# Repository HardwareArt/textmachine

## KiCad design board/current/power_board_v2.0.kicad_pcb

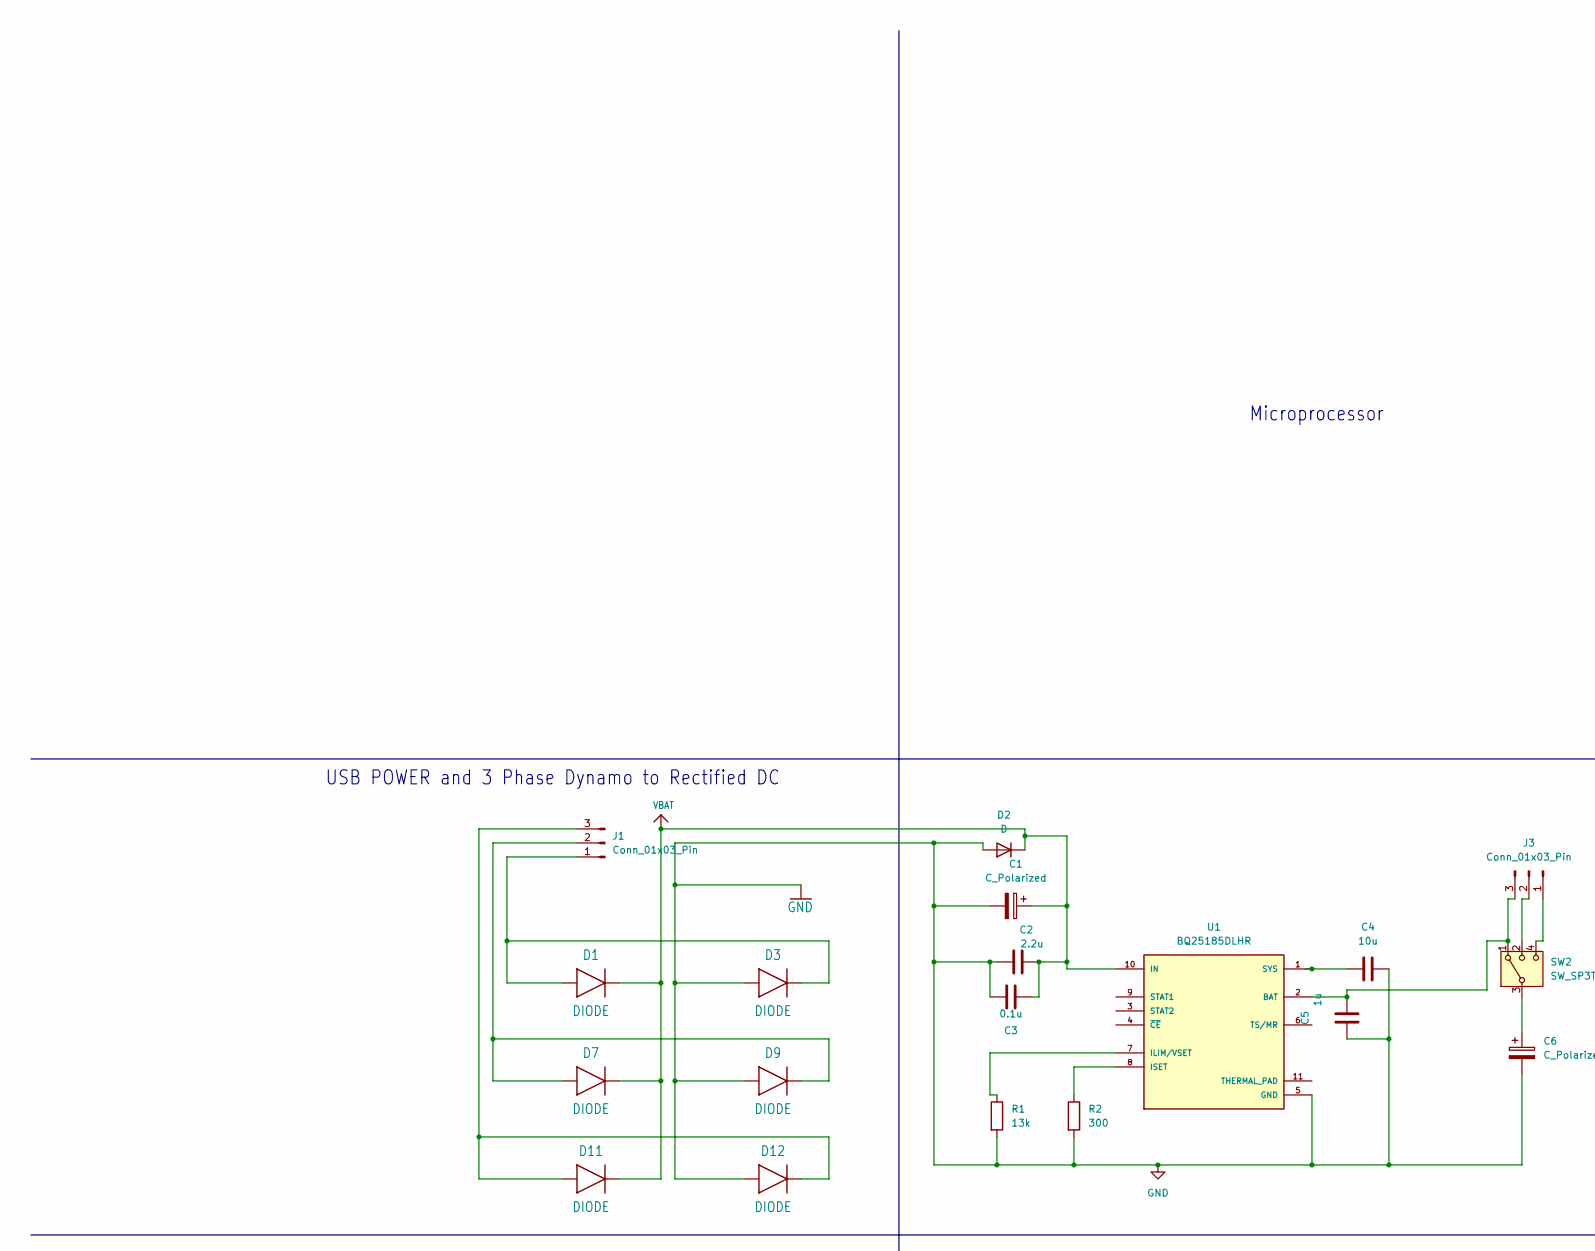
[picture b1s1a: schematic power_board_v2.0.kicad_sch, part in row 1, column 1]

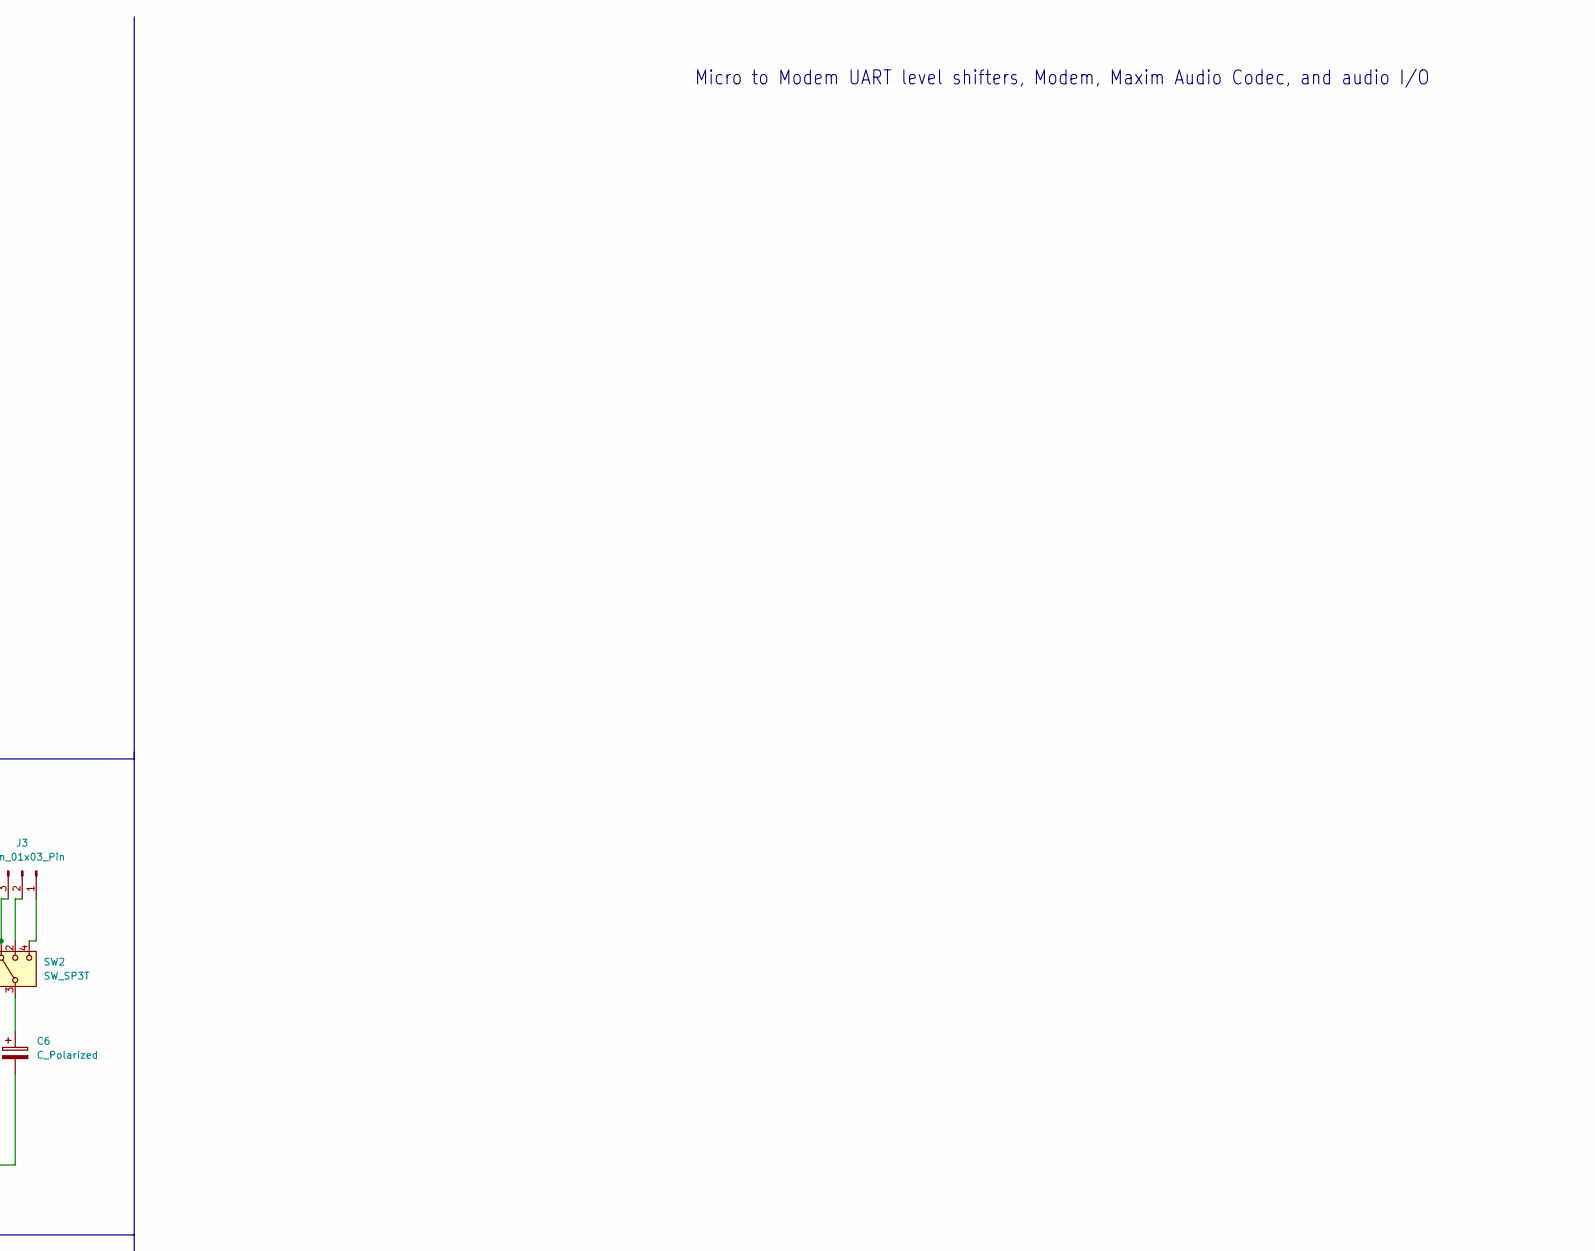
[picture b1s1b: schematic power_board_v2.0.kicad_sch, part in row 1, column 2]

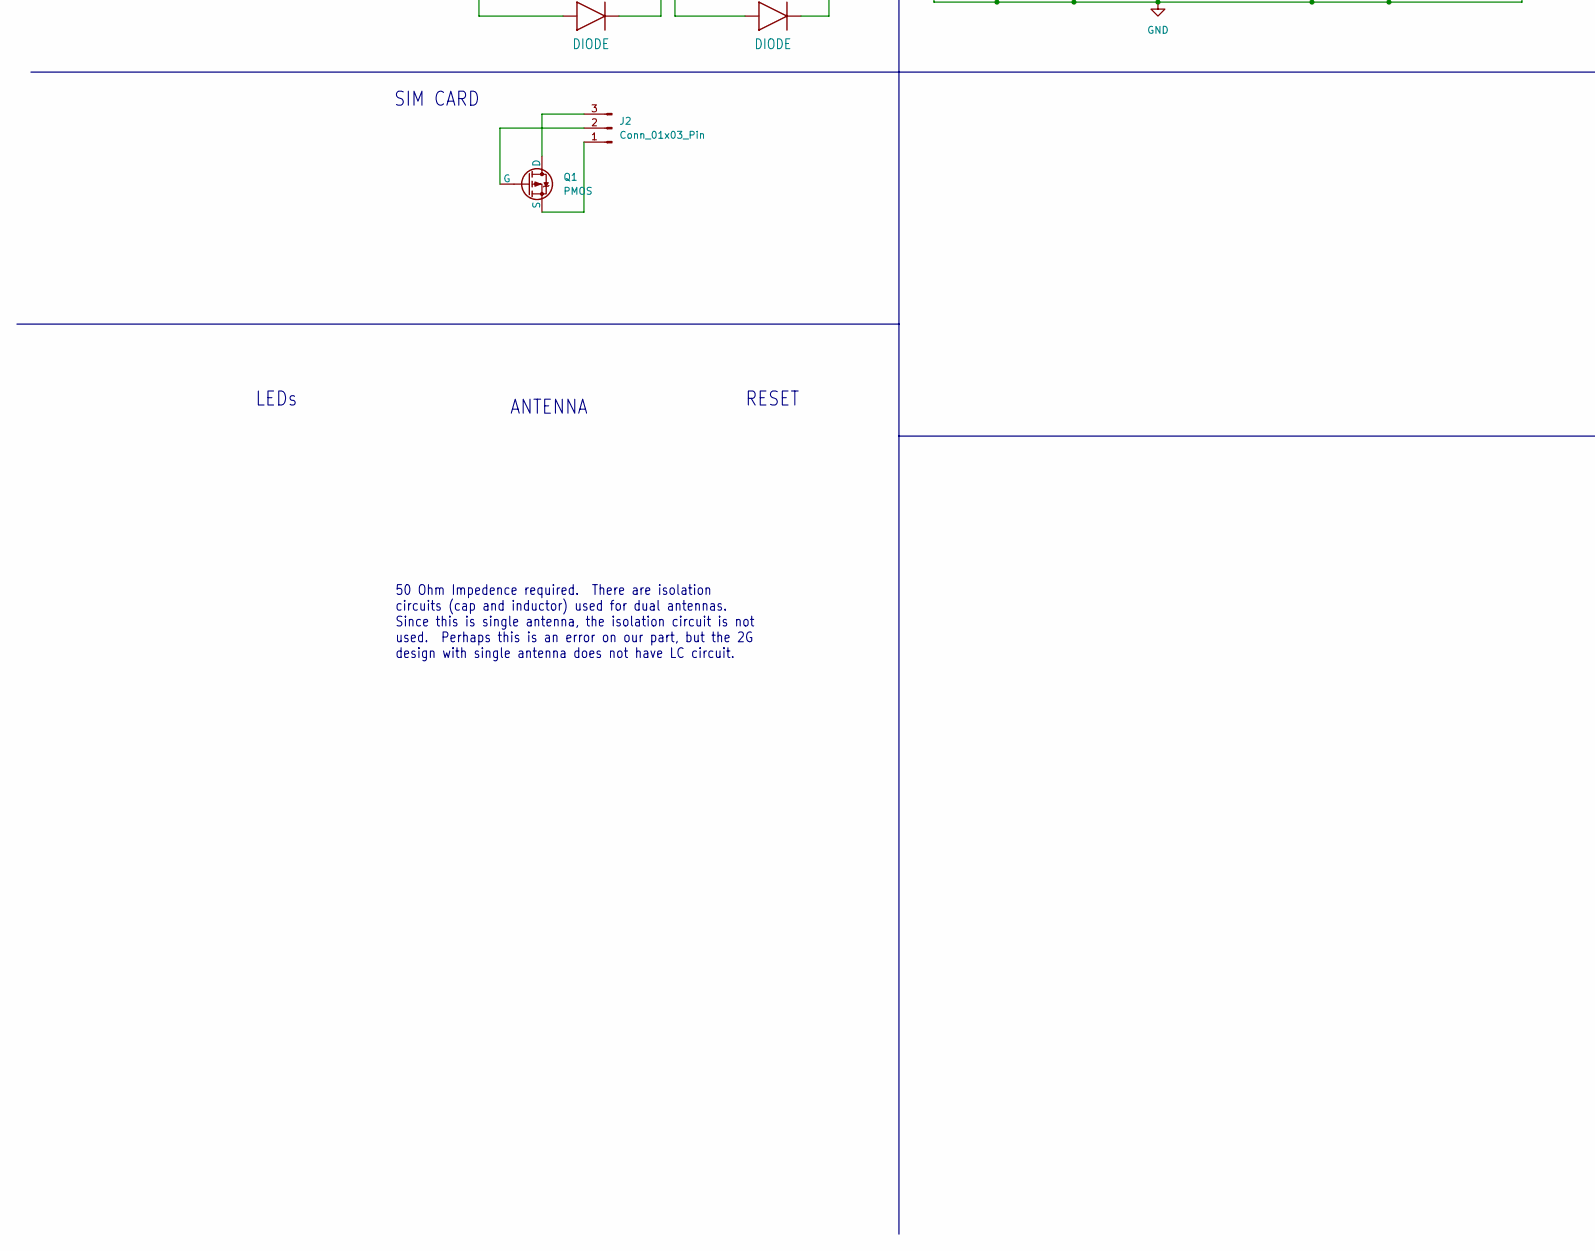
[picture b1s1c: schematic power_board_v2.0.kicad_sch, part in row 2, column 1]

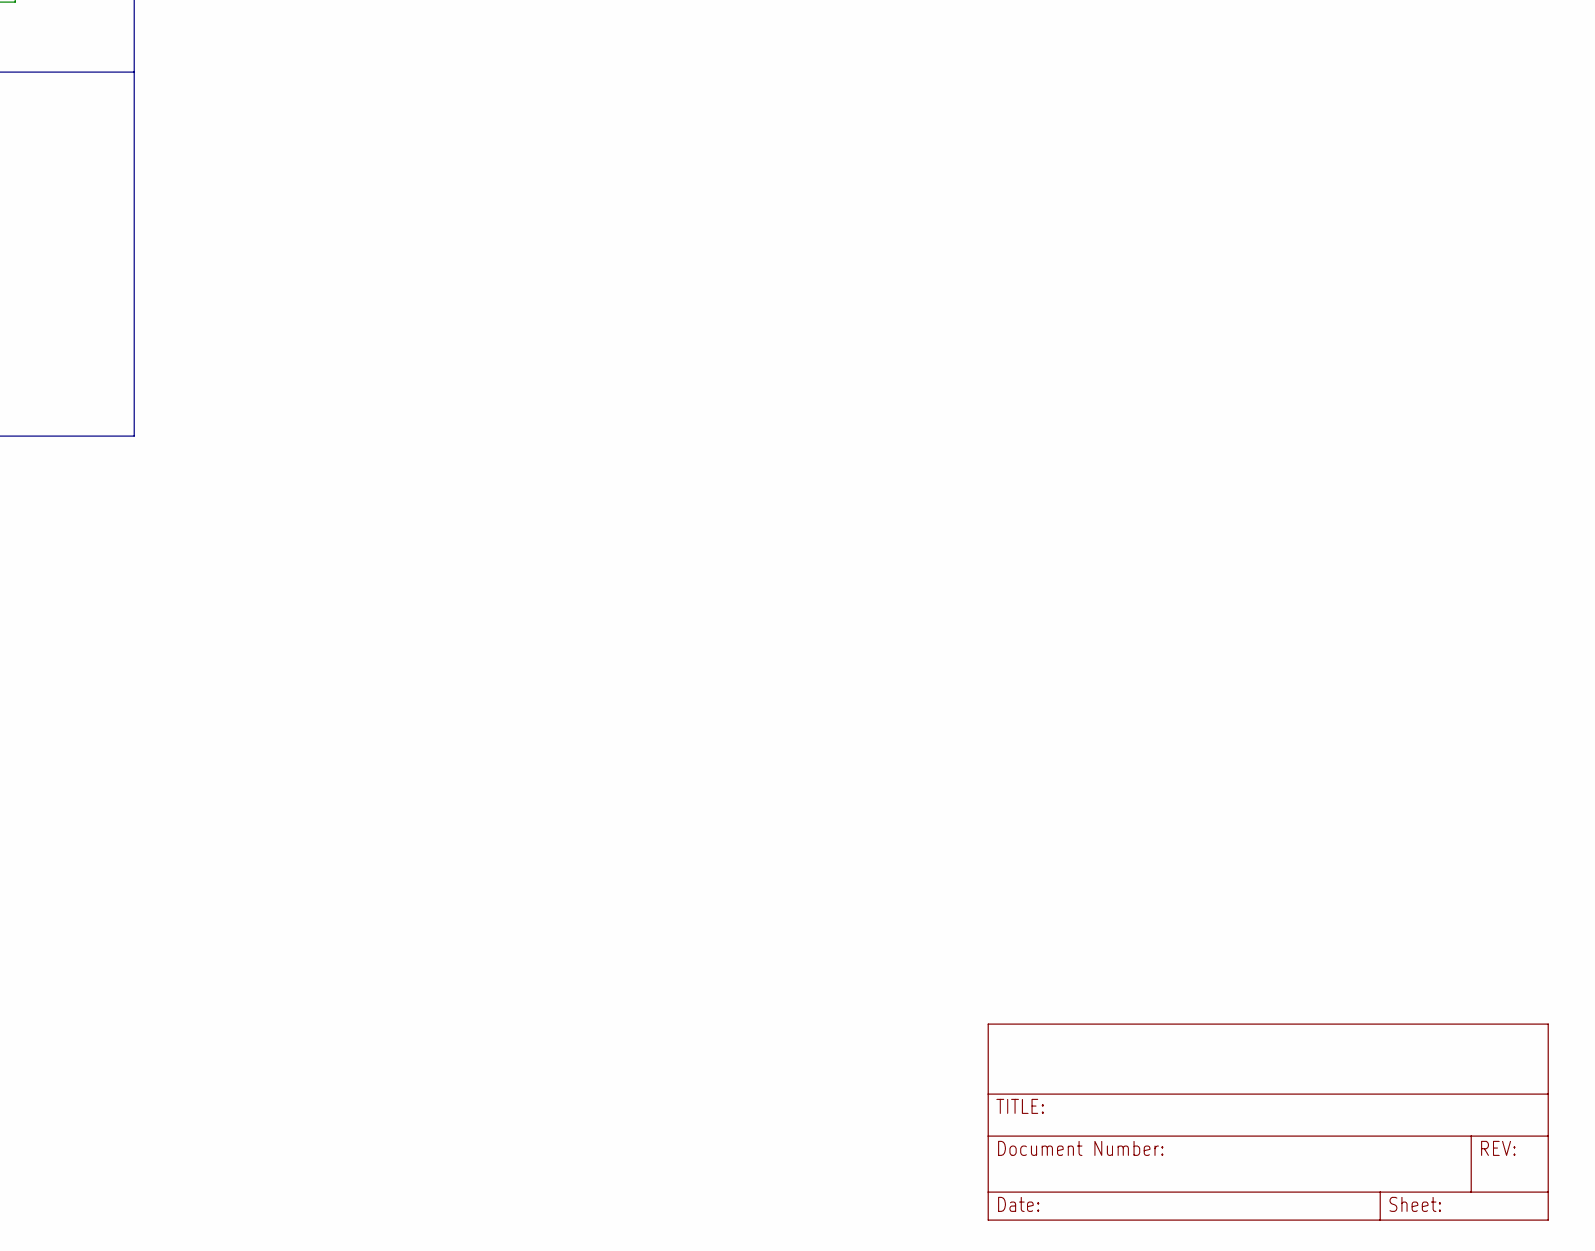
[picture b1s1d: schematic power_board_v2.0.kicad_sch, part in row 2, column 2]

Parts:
C1, C6: C_Polarized; CP_Radial_D8.0mm_P5.00mm
C2: 2.2u; C_0402_1005Metric
C3: 0.1u; C_0402_1005Metric
C4: 10u; C_0402_1005Metric
C5: 1u; C_0402_1005Metric
D1, D3, D7, D9, D11, D12: DIODE; D_SOD-123
D2: D; D_DO-15_P10.16mm_Horizontal
J1, J2, J3: Conn_01x03_Pin; PinHeader_1x03_P2.54mm_Vertical
Q1: PMOS; SOT-23
R1: 13k; R_01005_0402Metric
R2: 300; R_01005_0402Metric
SW2: SW_SP3T; SW_Push_2P1T_Toggle_CK_PVA1xxH1xxxxxxV2
U1: BQ25185DLHR; Texas_DLH0010A_WSON-10-1EP_2.2x2mm_P0.4mm_EP0.9x1.5mm; PARTREV OCTOBER 2023

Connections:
GND: C1.2, C2.1, C3.1, C4.2, C5.1, C6.2, D2.2 (A), D3.2 (A), D9.2 (A), D12.2 (A), R1.2, R2.2, U1.5 (GND)
unnamed: C6.1, SW2.3
unnamed: D1.2 (A), D3.1 (C), J1.1
unnamed: D7.2 (A), D9.1 (C), J1.2
unnamed: D11.2 (A), D12.1 (C), J1.3
unnamed: J2.1, Q1.3 (S)
unnamed: J2.2, Q1.2 (G)
unnamed: J2.3, Q1.1 (D)
unnamed: J3.1, SW2.4
unnamed: J3.2, SW2.2
unnamed: C5.2, J3.3, SW2.1, U1.2 (BAT)
unnamed: R1.1, U1.7 (ILIM/VSET)
unnamed: R2.1, U1.8 (ISET)
unnamed: C4.1, U1.1 (SYS)
VBAT: C1.1, C2.2, C3.2, D1.1 (C), D2.1 (K), D7.1 (C), D11.1 (C), U1.10 (IN)

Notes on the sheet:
50 Ohm Impedence required. There are isolation circuits (cap and inductor) used for dual antennas. Since this is single antenna, the isolation circuit is not used. Perhaps this is an error on our part, but the 2G design with single antenna does not have LC circuit.
Micro to Modem UART level shifters, Modem, Maxim Audio Codec, and audio I/O
RESET
USB POWER and 3 Phase Dynamo to Rectified DC
ANTENNA
SIM CARD
Microprocessor
LEDs

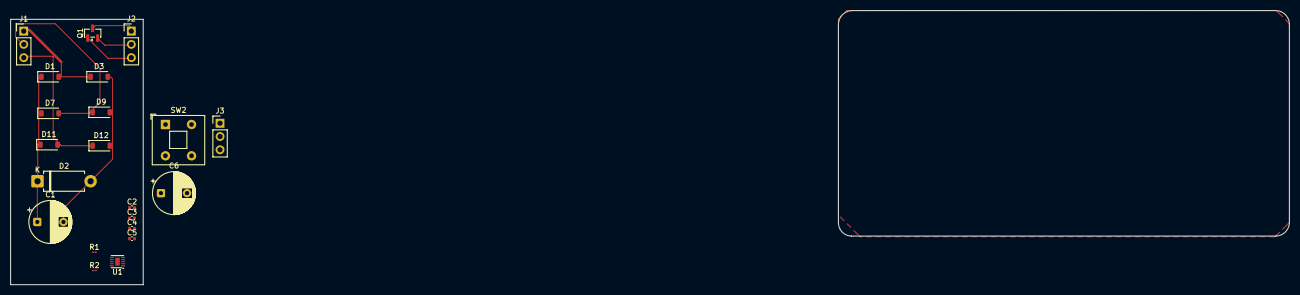
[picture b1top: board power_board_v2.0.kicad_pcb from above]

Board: 2 copper layers, 25.4 x 50.8 mm, 21 parts (0 on the bottom side), 15 nets.

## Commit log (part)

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2026-06-02 Added red screen before trying to connect to reduce ambiguity in power testing
2026-06-15 Add files via upload
    Added weekly status doc as PDF and keynote
2026-06-17 Cleaned up UI_COMPOSE's superficial flaws
2026-06-19 Solidified contacts logic with non volatile memory implementation and began single input debug implemntation, reworked keyboard so that it can work in different input modes, next step is implementing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
